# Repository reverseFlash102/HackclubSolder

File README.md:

# HackclubSolder
A simple pcb to turn on 2 led when it gets dark outside. Made By @SyamPaladugu

# Schematic

# PCB

# Function 
Turn on the LEDs when it gets dark. To be used as a keychain.

# BOM
2 Leds(Any Color)
2 220ohms resistors
1 photoresistor
1 Battery Holder
1 Battery

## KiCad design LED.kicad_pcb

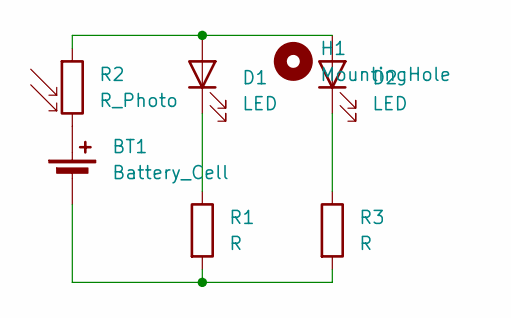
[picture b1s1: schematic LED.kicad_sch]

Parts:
BT1: Battery_Cell; BatteryHolder_Keystone_3034_1x20mm
D1, D2: LED; LED_D5.0mm
H1: MountingHole; MountingHole_2.1mm
R1, R3: R; R_Axial_DIN0207_L6.3mm_D2.5mm_P7.62mm_Horizontal
R2: R_Photo; R_LDR_5.1x4.3mm_P3.4mm_Vertical

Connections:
unnamed: BT1.1 (+), R2.2
unnamed: BT1.2 (-), R1.2, R3.2
unnamed: D1.2 (A), D2.2 (A), R2.1
unnamed: D1.1 (K), R1.1
unnamed: D2.1 (K), R3.1

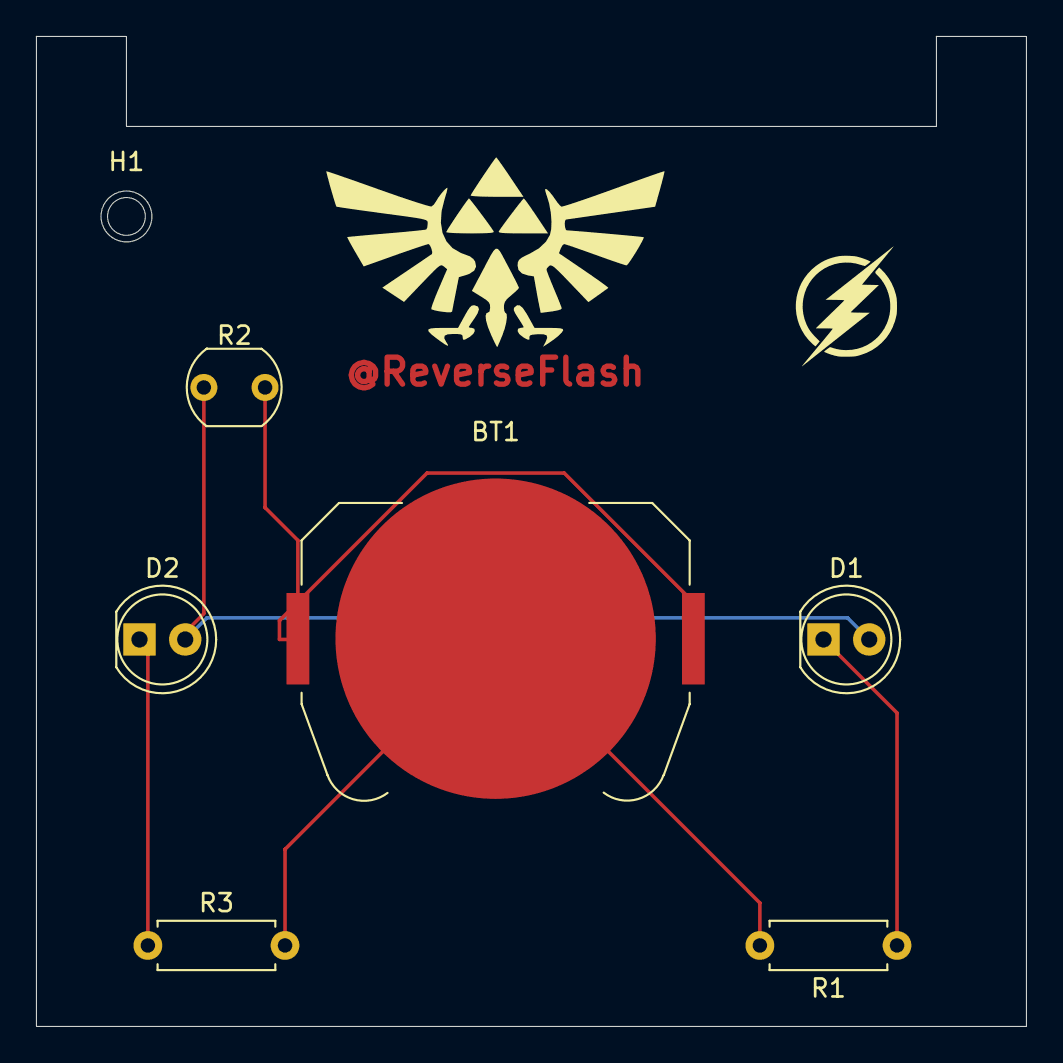
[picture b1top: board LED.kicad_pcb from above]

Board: 2 copper layers, 55.0 x 55.0 mm, 7 parts (0 on the bottom side), 5 nets.
